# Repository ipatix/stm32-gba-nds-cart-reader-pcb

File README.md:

# STM32 GBA NDS Reader PCB

## Overview

In this repository you can find the hardware/PCB files, which belong to the [software](https://github.com/ipatix/stm32-gba-nds-cart-reader), which has been on my Github account for quite while.

This PCB hardware allows you to physically communicate with NDS, DSi, GBA, and GBC carts (GBA/GBC switching via 5V/3V3 jumper).
Anything else related to the funcionality is part of the software and not explained here.

## Programming

The firmware is flashed to the STM32 via its serial programming interface.
Set the jumpers BOOT0=1 and BOOT1=0 to start the microcontroller.
You can then use the stm32flash utility to program the microcontroller via UART.

## Components

All of the components except the card headers should be avaiable on Mouser or other distributers.
The card headers I orderd on Aliexpress, and they were probably not much more than $1 a piece.
Though, they may be difficult to source in the future.

## Bugs

I ordered one batch of PCBs of this design.
Since then I never fixed the bugs that I discovered later.
Here is a list of known bugs:
- USB D+ line is missing the pull-up resistor.
  It's a bit tricky, but you can connect D+ to 3V3 on C20 using a 1.5k resistor.
- The direction pin U2 and U3 should have had pull-up/down resistor.
  That is because one of the STM32's boot pins is connected to one of the IOs of U2.
  This is a problem because the direction of IC U2 is undefined and may drive the BOOT1 pin before the STM32 has booted up.
  For some reason this was never turned out to be a problem on the boards I've tested, but this is definitely an issue that should have been fixed.

## General Design Improvements

So what did I not do thing A or thing B better in this design?
Well, turns out, I was learning PCB design.

Yes, resistor arrays are a thing and are probably much easier to solder by hand than the countless 0402 resistors/capacitors on the PCB.

Yes, it would have been more appropriate to use a more standard 74xx245 bus transceiver.
Perhaps they were even completely unnecessary, since the STM32 does have some IO banks, which are 5V tolerant and 5V game cards would probably detect 3.3V as logic high...

## History

This project was originally designed in EAGLE version 7.
In this repo you can only find the conversion to KiCAD, since I personally don't use EAGLE anymore and KiCAD is more accessible.
However, I don't know how reliable the conversion is, so it's possible there are some bugs.

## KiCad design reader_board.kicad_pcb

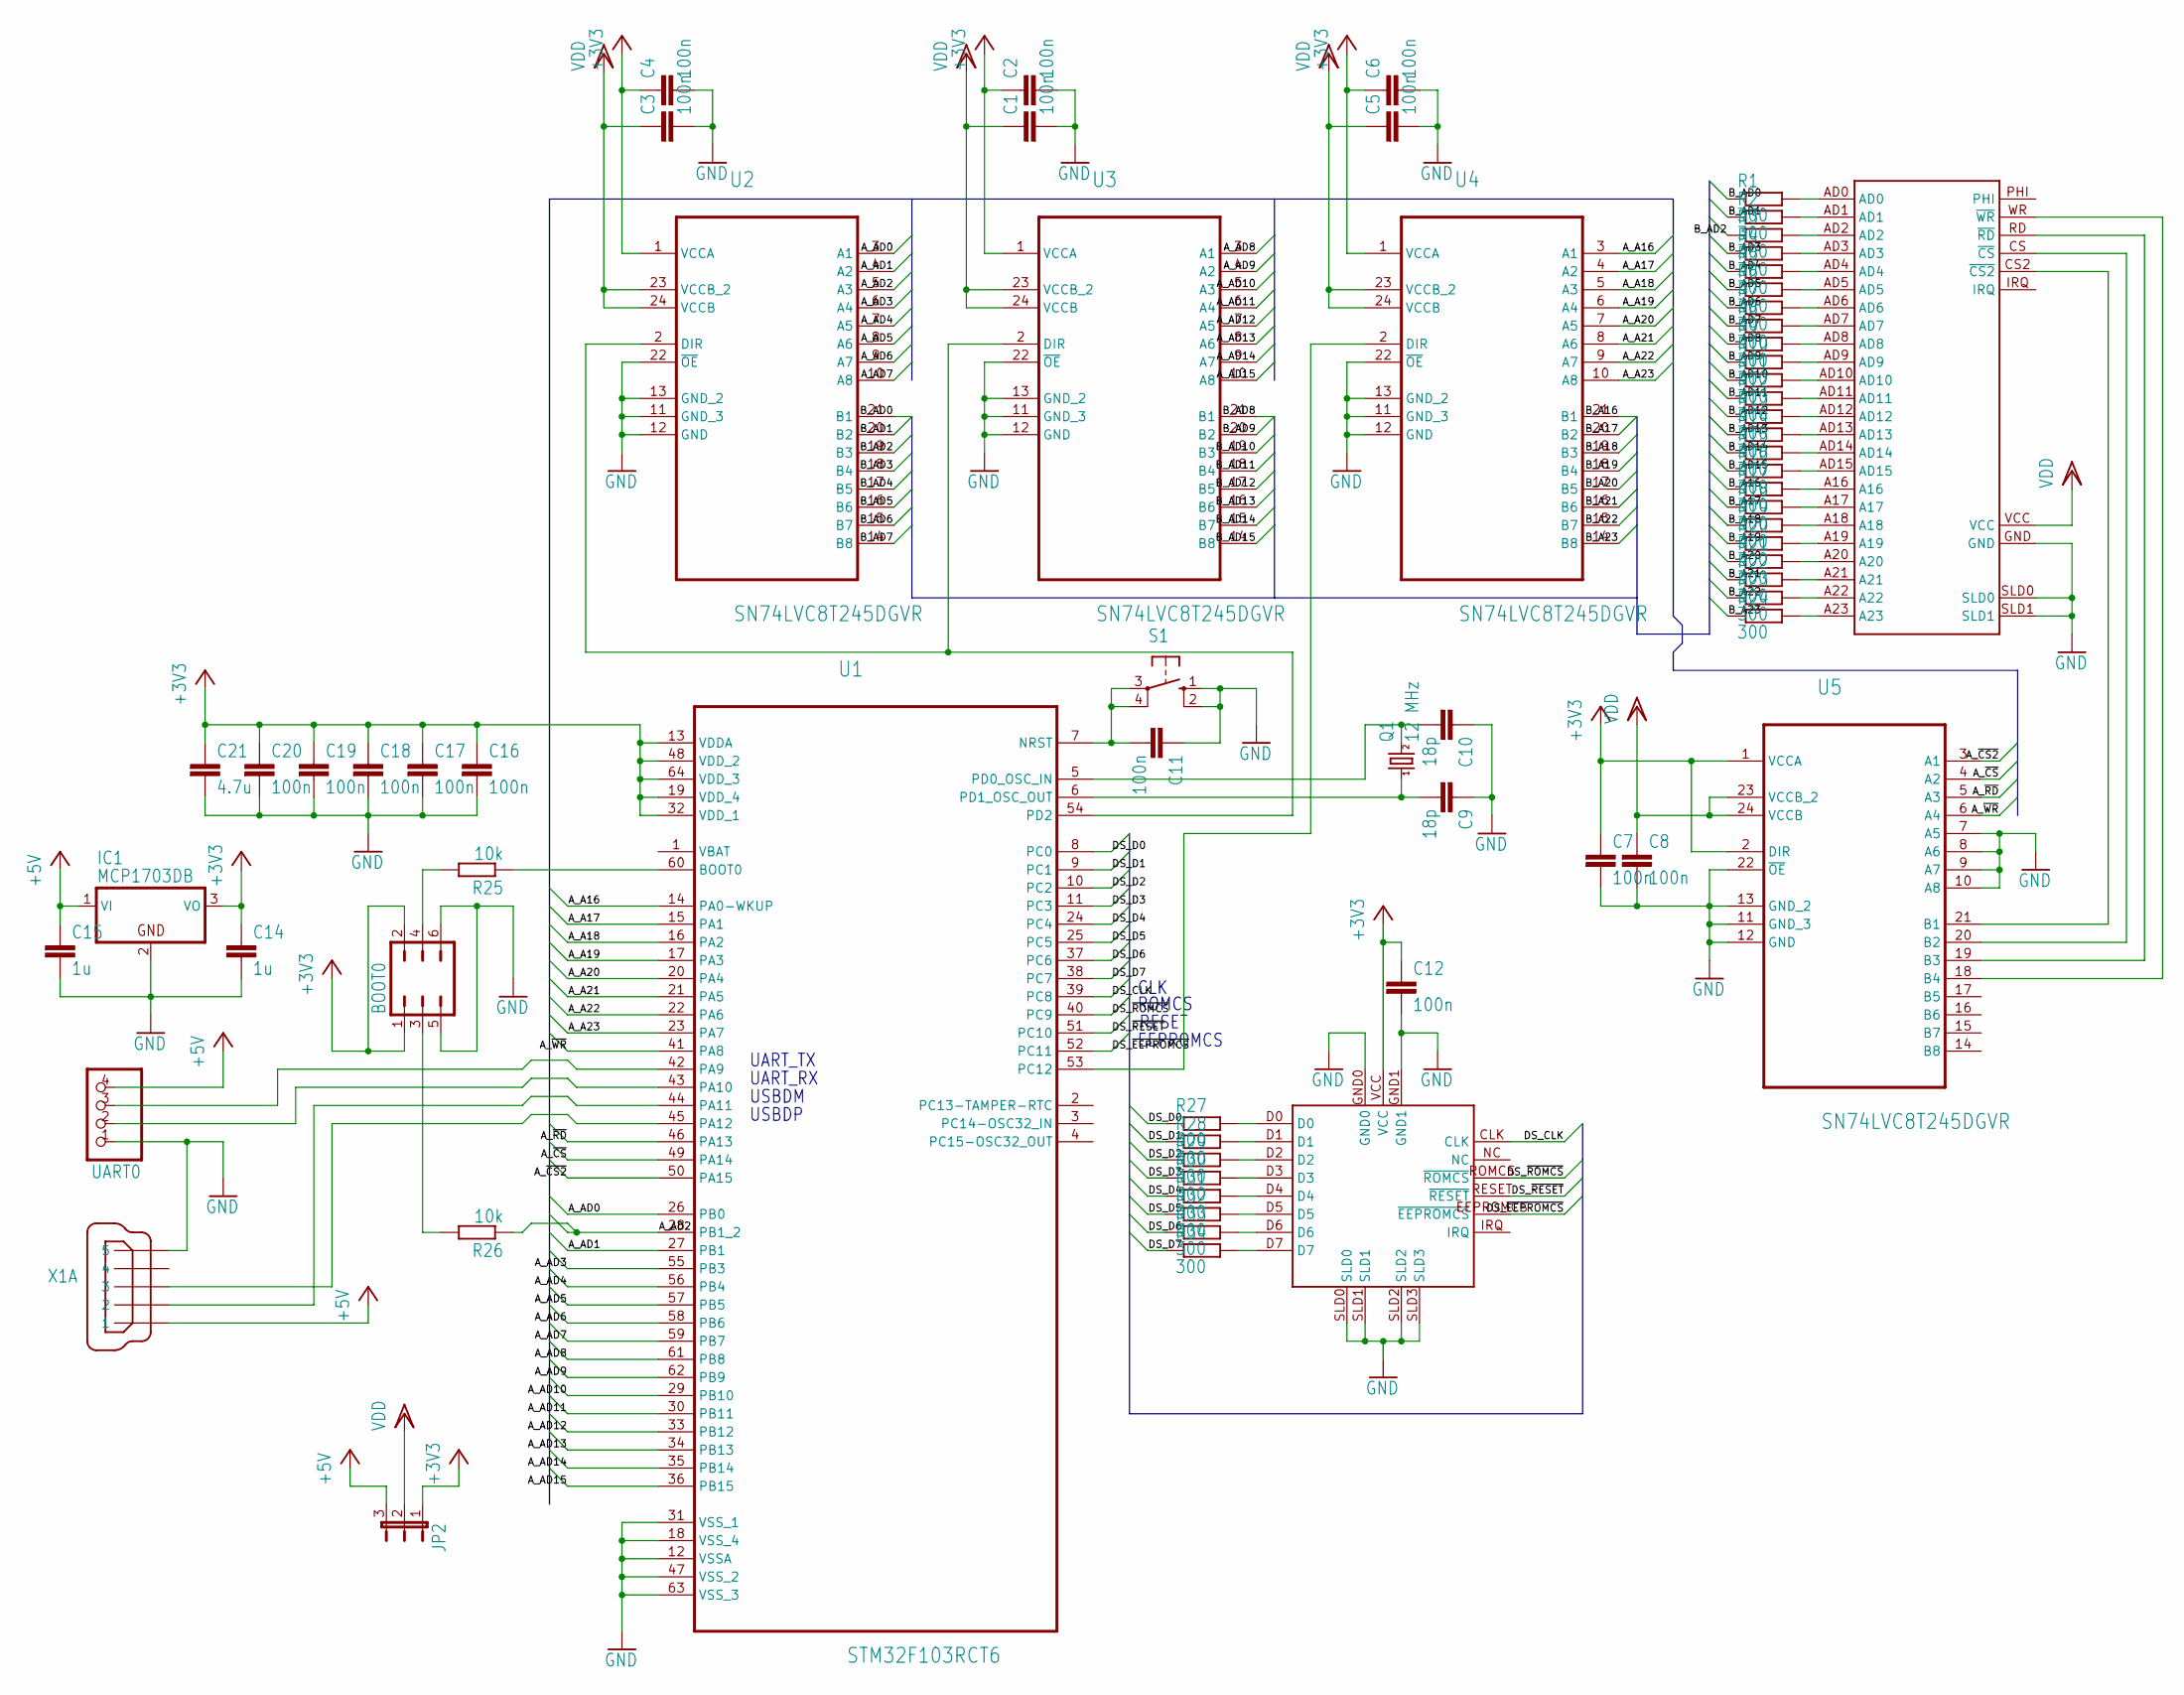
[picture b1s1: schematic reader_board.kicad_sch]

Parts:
BOOT0: JP3Q
C1, C2, C3, C4, C5, C6, C7, C8, C11, C12, C16, C17, C18, C19, C20: 100n; C0402
C9, C10: 18p; C0402
C14, C15: 1u; C0805
C21: 4.7u; C0805
IC1: MCP1703DB; SOT223
JP2: JP2E; JP2
Q1: 12 MHz; HC49UP
R1, R2, R3, R4, R5, R6, R7, R8, R9, R10, R11, R12, R13, R14, R15, R16, R17, R18, R19, R20, R21, R22, R23, R24, R27, R28, R29, R30, R31, R32, R33, R34: 300; R0402
R25, R26: 10k; R0402
S1: 10-XX; B3F-10XX
U1: STM32F103RCT6; QFP50P1200X1200X160-64N
U2, U3, U4, U5: SN74LVC8T245DGVR; SOP40P640X120-24N
U$1: GBA_SOCKET
U$2: NDSL_SOCKET
UART0: PINHD-1X4; 1X04
X1: MINI-USB_SHIELD5P4-32005-400; 32005-400

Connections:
+3V3: BOOT0.1, BOOT0.2, C2.1, C4.1, C6.1, C7.1, C12.1, C14.1, C16.1, C17.1, C18.1, C19.1, C20.1, C21.1, IC1.3 (VO), JP2.1, U1.13 (VDDA), U1.19 (VDD_4), U1.32 (VDD_1), U1.48 (VDD_2), U1.64 (VDD_3), U2.1 (VCCA), U3.1 (VCCA), U4.1 (VCCA), U5.1 (VCCA), U5.2 (DIR), U$2.VCC
+5V: C15.1, IC1.1 (VI), JP2.3, UART0.4, X1.1
AD_DIR: U1.54 (PD2), U2.2 (DIR), U3.2 (DIR)
A_A16: U1.14 (PA0-WKUP), U4.3 (A1)
A_A17: U1.15 (PA1), U4.4 (A2)
A_A18: U1.16 (PA2), U4.5 (A3)
A_A19: U1.17 (PA3), U4.6 (A4)
A_A20: U1.20 (PA4), U4.7 (A5)
A_A21: U1.21 (PA5), U4.8 (A6)
A_A22: U1.22 (PA6), U4.9 (A7)
A_A23: U1.23 (PA7), U4.10 (A8)
A_AD0: U1.26 (PB0), U2.3 (A1)
A_AD1: U1.27 (PB1), U2.4 (A2)
A_AD2: R26.1, U1.28 (PB1_2), U2.5 (A3)
A_AD3: U1.55 (PB3), U2.6 (A4)
A_AD4: U1.56 (PB4), U2.7 (A5)
A_AD5: U1.57 (PB5), U2.8 (A6)
A_AD6: U1.58 (PB6), U2.9 (A7)
A_AD7: U1.59 (PB7), U2.10 (A8)
A_AD8: U1.61 (PB8), U3.3 (A1)
A_AD9: U1.62 (PB9), U3.4 (A2)
A_AD10: U1.29 (PB10), U3.5 (A3)
A_AD11: U1.30 (PB11), U3.6 (A4)
A_AD12: U1.33 (PB12), U3.7 (A5)
A_AD13: U1.34 (PB13), U3.8 (A6)
A_AD14: U1.35 (PB14), U3.9 (A7)
A_AD15: U1.36 (PB15), U3.10 (A8)
A_DIR: U1.53 (PC12), U4.2 (DIR)
A_~CS2: U1.50 (PA15), U5.3 (A1)
A_~CS: U1.49 (PA14), U5.4 (A2)
A_~RD: U1.46 (PA13), U5.5 (A3)
A_~WR: U1.41 (PA8), U5.6 (A4)
BOOT0: R25.1, U1.60 (BOOT0)
B_A16: R17.1, U4.21 (B1)
B_A17: R18.1, U4.20 (B2)
B_A18: R19.1, U4.19 (B3)
B_A19: R20.1, U4.18 (B4)
B_A20: R21.1, U4.17 (B5)
B_A21: R22.1, U4.16 (B6)
B_A22: R23.1, U4.15 (B7)
B_A23: R24.1, U4.14 (B8)
B_AD0: R1.1, U2.21 (B1)
B_AD1: R2.1, U2.20 (B2)
B_AD2: R3.1, U2.19 (B3)
B_AD3: R4.1, U2.18 (B4)
B_AD4: R5.1, U2.17 (B5)
B_AD5: R6.1, U2.16 (B6)
B_AD6: R7.1, U2.15 (B7)
B_AD7: R8.1, U2.14 (B8)
B_AD8: R9.1, U3.21 (B1)
B_AD9: R10.1, U3.20 (B2)
B_AD10: R11.1, U3.19 (B3)
B_AD11: R12.1, U3.18 (B4)
B_AD12: R13.1, U3.17 (B5)
B_AD13: R14.1, U3.16 (B6)
B_AD14: R15.1, U3.15 (B7)
B_AD15: R16.1, U3.14 (B8)
B_~CS2: U5.21 (B1), U$1.~CS2 (~CS2)
B_~CS: U5.20 (B2), U$1.~CS (~CS)
B_~RD: U5.19 (B3), U$1.~RD (~RD)
B_~WR: U5.18 (B4), U$1.~WR (~WR)
DS_CLK: U1.39 (PC8), U$2.CLK
DS_D0: R27.1, U1.8 (PC0)
DS_D1: R28.1, U1.9 (PC1)
DS_D2: R29.1, U1.10 (PC2)
DS_D3: R30.1, U1.11 (PC3)
DS_D4: R31.1, U1.24 (PC4)
DS_D5: R32.1, U1.25 (PC5)
DS_D6: R33.1, U1.37 (PC6)
DS_D7: R34.1, U1.38 (PC7)
DS_~EEPROMCS: U1.52 (PC11), U$2.~EEPROMCS (~EEPROMCS)
DS_~RESET: U1.51 (PC10), U$2.~RESET (~RESET)
DS_~ROMCS: U1.40 (PC9), U$2.~ROMCS (~ROMCS)
GND: BOOT0.5, BOOT0.6, C1.2, C2.2, C3.2, C4.2, C5.2, C6.2, C7.2, C8.2, C9.1, C10.1, C11.1, C12.2, C14.2, C15.2, C16.2, C17.2, C18.2, C19.2, C20.2, C21.2, IC1.2 (GND), S1.1 (S), S1.2 (S1), U1.12 (VSSA), U1.18 (VSS_4), U1.31 (VSS_1), U1.47 (VSS_2), U1.63 (VSS_3), U2.11 (GND_3), U2.12 (GND), U2.13 (GND_2), U2.22 (~OE), U3.11 (GND_3), U3.12 (GND), U3.13 (GND_2), U3.22 (~OE), U4.11 (GND_3), U4.12 (GND), U4.13 (GND_2), U4.22 (~OE), U5.7 (A5), U5.8 (A6), U5.9 (A7), U5.10 (A8), U5.11 (GND_3), U5.12 (GND), U5.13 (GND_2), U5.22 (~OE), U$1.GND, U$1.SLD0, U$1.SLD1, U$2.GND0, U$2.GND1, U$2.SLD0, U$2.SLD1, U$2.SLD2, U$2.SLD3, UART0.1, X1.5
unnamed: R1.2, U$1.AD0
unnamed: R2.2, U$1.AD1
unnamed: R3.2, U$1.AD2
unnamed: R4.2, U$1.AD3
unnamed: R5.2, U$1.AD4
unnamed: R6.2, U$1.AD5
unnamed: R7.2, U$1.AD6
unnamed: R8.2, U$1.AD7
unnamed: R9.2, U$1.AD8
unnamed: R10.2, U$1.AD9
unnamed: R11.2, U$1.AD10
unnamed: R12.2, U$1.AD11
unnamed: R13.2, U$1.AD12
unnamed: R14.2, U$1.AD13
unnamed: R15.2, U$1.AD14
unnamed: R16.2, U$1.AD15
unnamed: R17.2, U$1.A16
unnamed: R18.2, U$1.A17
unnamed: R19.2, U$1.A18
unnamed: R20.2, U$1.A19
unnamed: R21.2, U$1.A20
unnamed: R22.2, U$1.A21
unnamed: R23.2, U$1.A22
unnamed: R24.2, U$1.A23
unnamed: BOOT0.4, R25.2
unnamed: BOOT0.3, R26.2
unnamed: C11.2, S1.3, S1.4 (P1), U1.7 (NRST)
unnamed: C9.2, Q1.1, U1.6 (PD1_OSC_OUT)
unnamed: C10.2, Q1.2, U1.5 (PD0_OSC_IN)
unnamed: R27.2, U$2.D0
unnamed: R28.2, U$2.D1
unnamed: R29.2, U$2.D2
unnamed: R30.2, U$2.D3
unnamed: R31.2, U$2.D4
unnamed: R32.2, U$2.D5
unnamed: R33.2, U$2.D6
unnamed: R34.2, U$2.D7
unnamed: U1.44 (PA11), X1.2
unnamed: U1.45 (PA12), X1.3
UART_RX: U1.43 (PA10), UART0.2
UART_TX: U1.42 (PA9), UART0.3
VDD: C1.1, C3.1, C5.1, C8.1, JP2.2, U2.23 (VCCB_2), U2.24 (VCCB), U3.23 (VCCB_2), U3.24 (VCCB), U4.23 (VCCB_2), U4.24 (VCCB), U5.23 (VCCB_2), U5.24 (VCCB), U$1.VCC

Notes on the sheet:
ROMCS
USBDP
UART_RX
USBDM
CLK
RESET
UART_TX
EEPROMCS

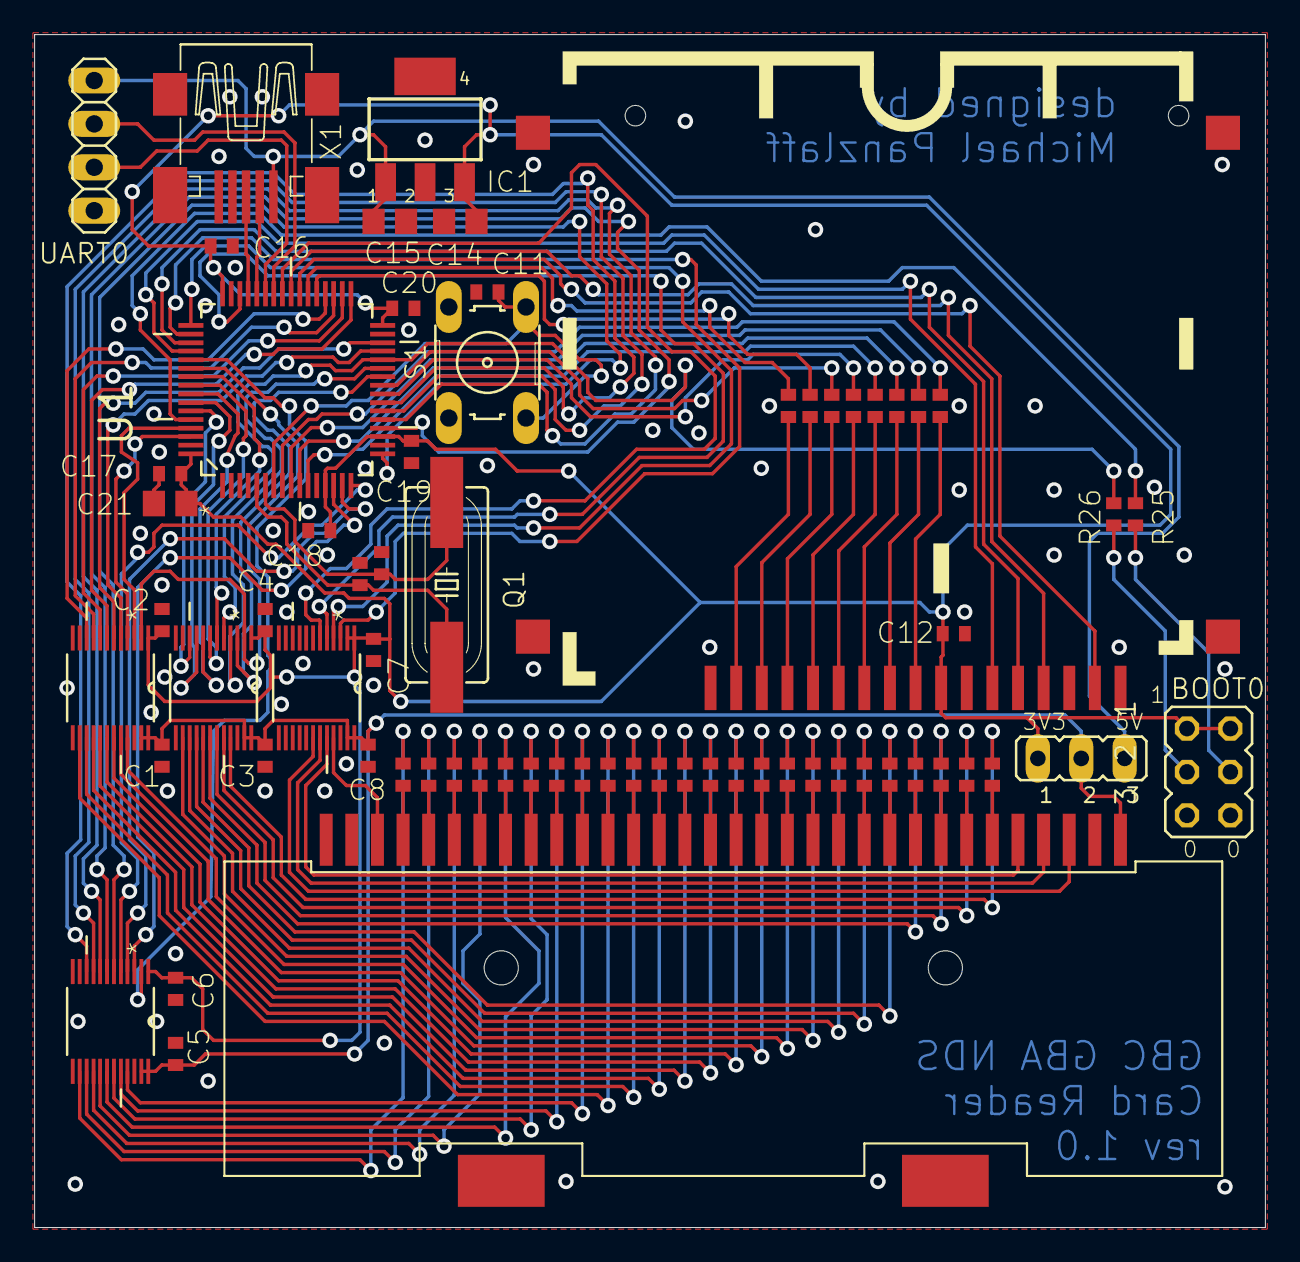
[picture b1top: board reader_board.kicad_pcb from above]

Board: 2 copper layers, 72.1 x 69.8 mm, 68 parts (0 on the bottom side), 116 nets.

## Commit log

2025-04-03 add project to version control
2025-04-03 add info about serial programming
